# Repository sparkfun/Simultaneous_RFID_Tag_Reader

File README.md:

SparkFun Simultaneous RFID Tag Reader Breakout
=============================================

[* SparkFun Simultaneous RFID Tag Reader Breakout](https://www.sparkfun.com/products/14066)

A breakout board the for UHF RFID module (M6E-NANO) from ThingMagic. 
Capable of reading multiple 860-920MHz UHF RFID tags at the same time with increased read distance. 
You can also write to tags to boot. 

Board works either as shield or as stand alone device (using a USB to Serial converter).

Repository Contents
-------------------

* **/Documentation** - Data sheets, additional product information
* **/Hardware** - Eagle design files (.brd, .sch)
* **/Libraries** - Libraries for use with the Simultaneous RFID Tag Reader
* **/Production** - Production panel files (.brd)

Documentation
--------------
* **[Library](https://github.com/sparkfun/SparkFun_Simultaneous_RFID_Tag_Reader_Library)** - Arduino library for the Tag Reader.
* **[Hookup Guide](https://learn.sparkfun.com/tutorials/simultaneous-rfid-tag-reader-hookup-guide)** - Basic hookup guide for the Tag Reader.
* **[SparkFun Fritzing repo](https://github.com/sparkfun/Fritzing_Parts)** - Fritzing diagrams for SparkFun products.
* **[SparkFun 3D Model repo](https://github.com/sparkfun/3D_Models)** - 3D models of SparkFun products. 

License Information
-------------------

This product is _**open source**_! 

Please review the LICENSE.md file for license information. 

If you have any questions or concerns on licensing, please contact techsupport@sparkfun.com.

Distributed as-is; no warranty is given.

- Your friends at SparkFun.

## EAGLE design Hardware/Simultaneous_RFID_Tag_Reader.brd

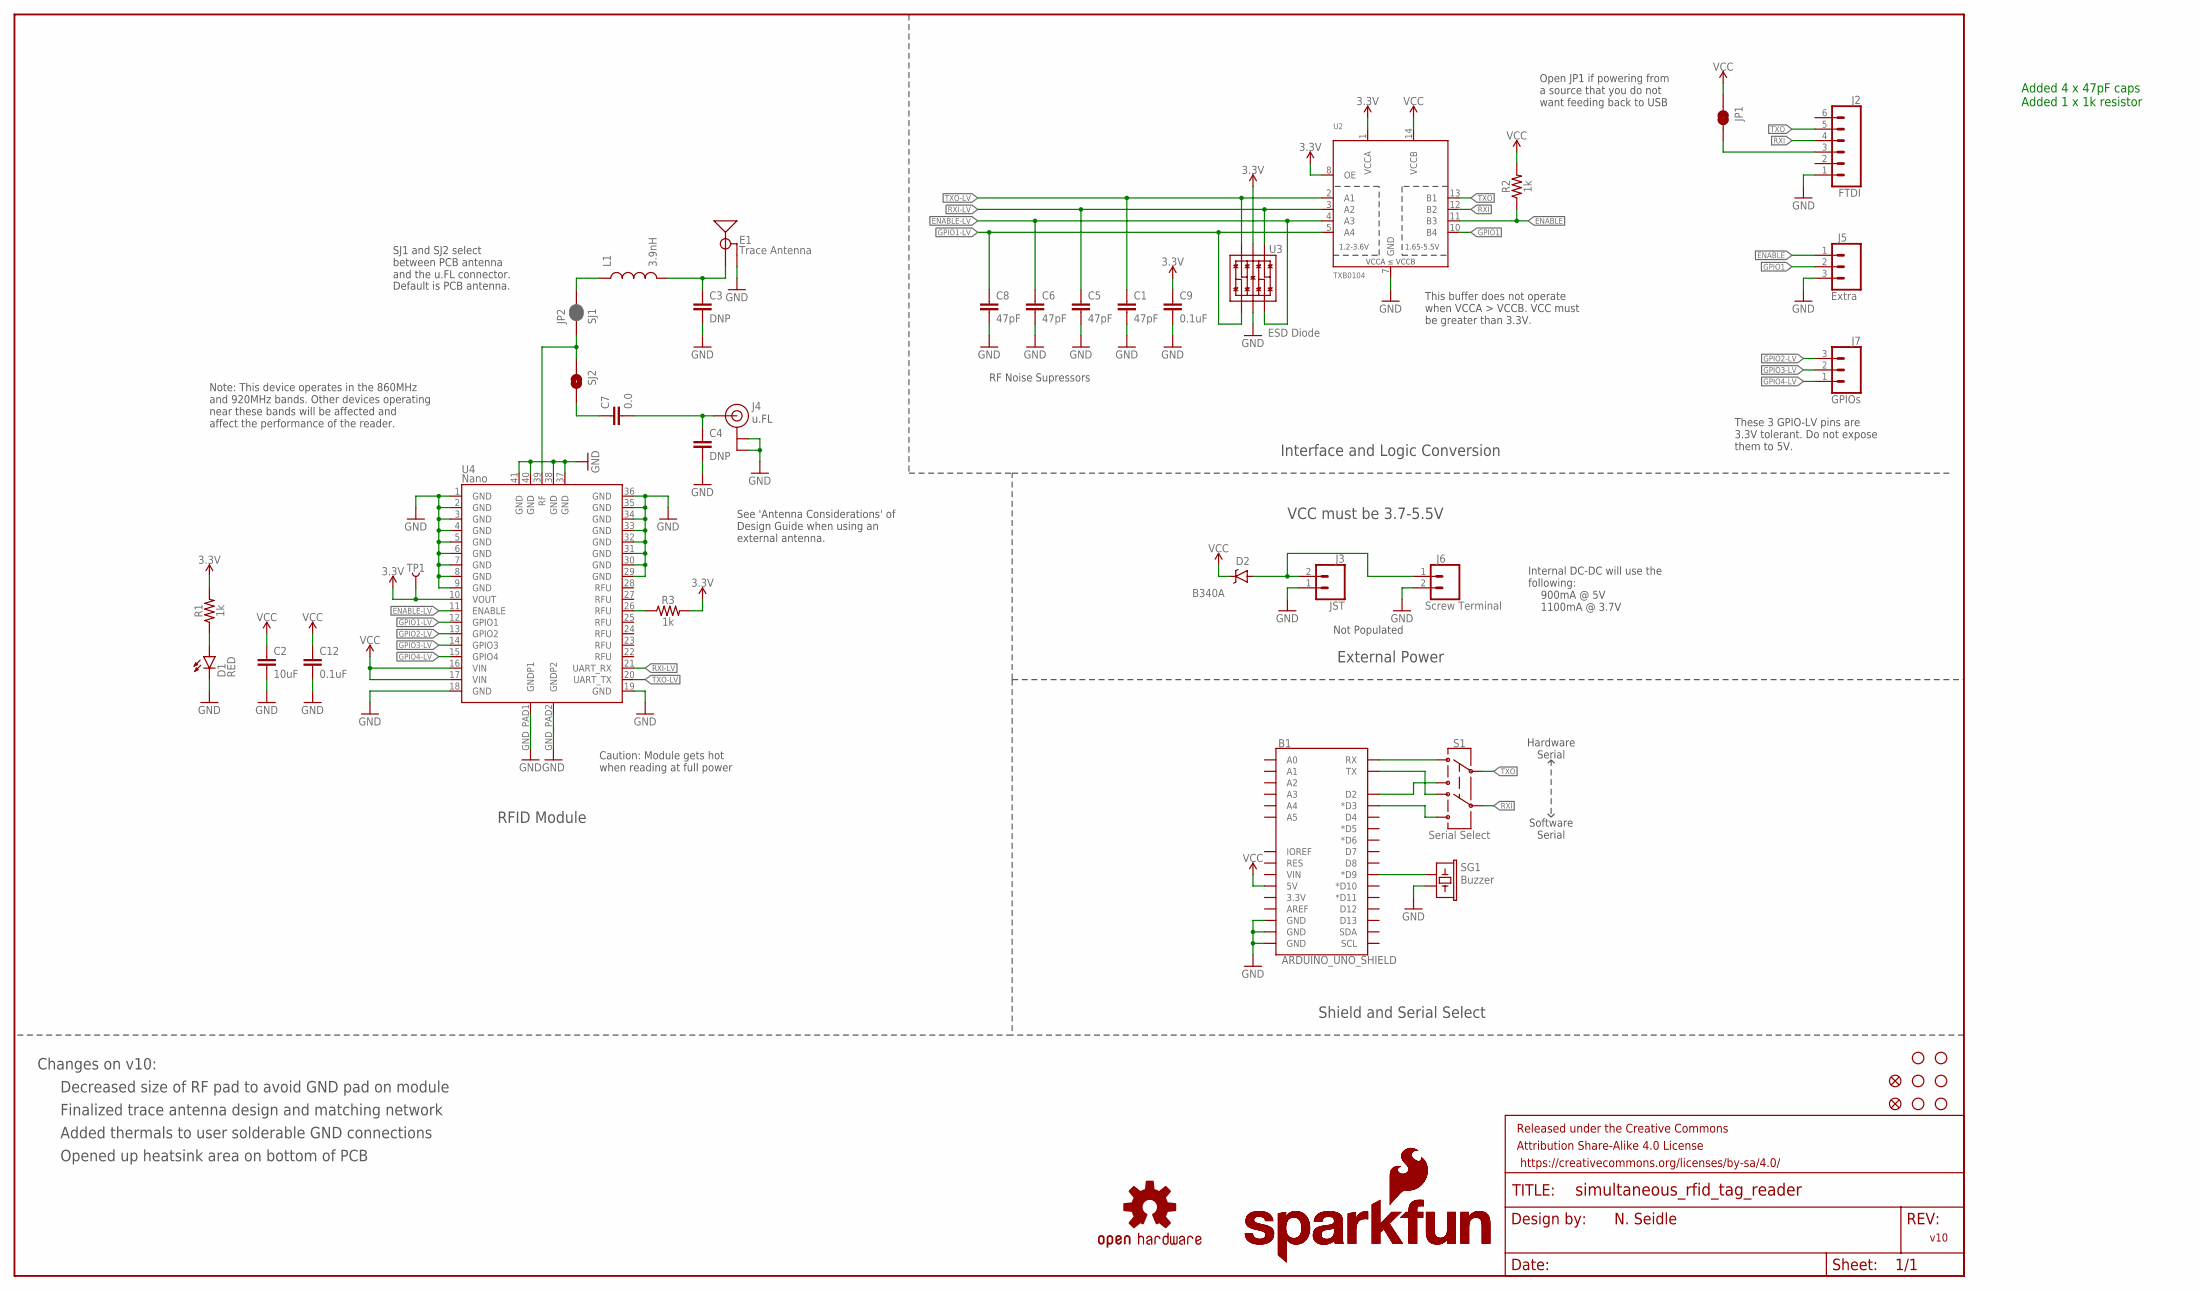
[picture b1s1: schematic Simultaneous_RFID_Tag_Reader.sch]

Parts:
B1: ARDUINO_UNO_SHIELD; UNO_R3_SHIELD
C1, C5, C6, C8: 47pF; 0603
C2: 10uF; 0805
C3, C4: DNP; 0603
C7: 0.0; 0603
C9, C12: 0.1uF; 0603
D1: RED; LED-0603
D2: B340A; SMA-DIODE
E1: Trace Antenna; 915MHZ_ANTENNA_TRIMBLE
FID1, FID2: FIDUCIAL1X2; FIDUCIAL-1X2
FRAME1: FRAME-LEDGER; CREATIVE_COMMONS
J2: FTDI; 1X06
J3: JST; JST-2-PTH
J4: U.FL
J5: Extra; 1X03
J6: Screw Terminal; SCREWTERMINAL-3.5MM-2
J7: GPIOs; 1X03
JP1: JUMPER-SMT_2_NC_TRACE_SILK; SMT-JUMPER_2_NC_TRACE_SILK
JP2: SJ1; SMT-JUMPER_2_NO_NO-SILK
L1: 3.9nH; 0603
LOGO1, LOGO3: SFE_LOGO_NAME_FLAME.1_INCH; SFE_LOGO_NAME_FLAME_.1
LOGO2: OSHW-LOGOS; OSHW-LOGO-S
R1, R2, R3: 1k; 0603
S1: Serial Select; SWITCH_DPDT_SMD_AYZ0202
SG1: Buzzer; BUZZER-CCV
SJ2: JUMPER-SMT_2_NO_NO-SILK; SMT-JUMPER_2_NO_NO-SILK
STANDOFF1, STANDOFF2, STANDOFF3, STANDOFF4, STANDOFF7, STANDOFF8: STAND-OFF
TP1: TEST-POINT3; PAD.03X.03
U2: TXB0104; SO14
U3: ESD Diode; SOT-23-6
U4: Nano; NANO_MODULE

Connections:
3.3V: C9.1, R1.2, R3.2, TP1.P$1, U2.1 (VCCA), U2.8 (OE), U3.5 (VCC), U4.10 (VOUT)
ANT3: JP2.1, SJ2.1, U4.39 (RF)
ENABLE: J5.1, R2.1, U2.11 (B3)
ENABLE-LV: C6.1, U2.4 (A3), U3.3 (IO2), U4.11 (ENABLE)
GND: B1.GND@0 (GND), B1.GND@1 (GND), B1.GND@2 (GND), C1.2, C2.2, C3.2, C4.2, C5.2, C6.2, C8.2, C9.2, C12.2, D1.C, E1.GND@1 (GND), E1.GND@2 (GND), E1.GND@3 (GND), J2.1, J3.1, J4.P$1 (GND), J4.P$2 (GND), J5.3, J6.2, SG1.- (2), U2.7 (GND), U3.2 (VSS), U4.1 (GND), U4.2 (GND), U4.3 (GND), U4.4 (GND), U4.5 (GND), U4.6 (GND), U4.7 (GND), U4.8 (GND), U4.9 (GND), U4.18 (GND), U4.19 (GND), U4.29 (GND), U4.30 (GND), U4.31 (GND), U4.32 (GND), U4.33 (GND), U4.34 (GND), U4.35 (GND), U4.36 (GND), U4.37 (GND), U4.38 (GND), U4.40 (GND), U4.41 (GND), U4.GND_PAD1 (GNDP1), U4.GND_PAD2 (GNDP2)
GPIO1: J5.2, U2.10 (B4)
GPIO1-LV: C8.1, U2.5 (A4), U3.1 (IO1), U4.12 (GPIO1)
GPIO2-LV: J7.3, U4.13 (GPIO2)
GPIO3-LV: J7.2, U4.14 (GPIO3)
GPIO4-LV: J7.1, U4.15 (GPIO4)
unnamed: C3.1, E1.ANT (SIGNAL), L1.2
unnamed: JP2.2, L1.1
unnamed: C7.1, SJ2.2
unnamed: R3.1, U4.26 (RFU)
unnamed: C4.1, C7.2, J4.P$3 (SIGNAL)
unnamed: D1.A, R1.1
unnamed: J2.3, JP1.2
unnamed: B1.RX, S1.1
unnamed: B1.TX, S1.4
unnamed: B1.D9 (*D9), SG1.+ (1)
unnamed: D2.A, J3.2, J6.1
RXI: J2.4, S1.5, U2.12 (B2)
RXI-LV: C5.1, U2.3 (A2), U3.4 (IO3), U4.21 (UART_RX)
SOFT-RX: B1.D2, S1.3
SOFT-TX: B1.D3 (*D3), S1.6
TXO: J2.5, S1.2, U2.13 (B1)
TXO-LV: C1.1, U2.2 (A1), U3.6 (IO4), U4.20 (UART_TX)
VCC: B1.5V, C2.1, C12.1, D2.C, JP1.1, R2.2, U2.14 (VCCB), U4.16 (VIN), U4.17 (VIN)

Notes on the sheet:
v10
N. Seidle
Interface and Logic Conversion
VCC must be 3.7-5.5V
Internal DC-DC will use the following: 900mA @ 5V 1100mA @ 3.7V
RFID Module
SJ1 and SJ2 select between PCB antenna and the u.FL connector.
Note: This device operates in the 860MHz and 920MHz bands. Other devices operating near these bands will be affected and affect the performance of the reader.
See 'Antenna Considerations' of Design Guide when using an external antenna.
u.FL
Hardware Serial
Software Serial
External Power
Shield and Serial Select
Default is PCB antenna.
Not Populated
Open JP1 if powering from a source that you do not want feeding back to USB
These 3 GPIO-LV pins are 3.3V tolerant. Do not expose them to 5V.
Decreased size of RF pad to avoid GND pad on module
Finalized trace antenna design and matching network
Changes on v10:
Added thermals to user solderable GND connections
Caution: Module gets hot when reading at full power
Opened up heatsink area on bottom of PCB
This buffer does not operate when VCCA > VCCB. VCC must be greater than 3.3V.
RF Noise Supressors
Added 4 x 47pF caps Added 1 x 1k resistor

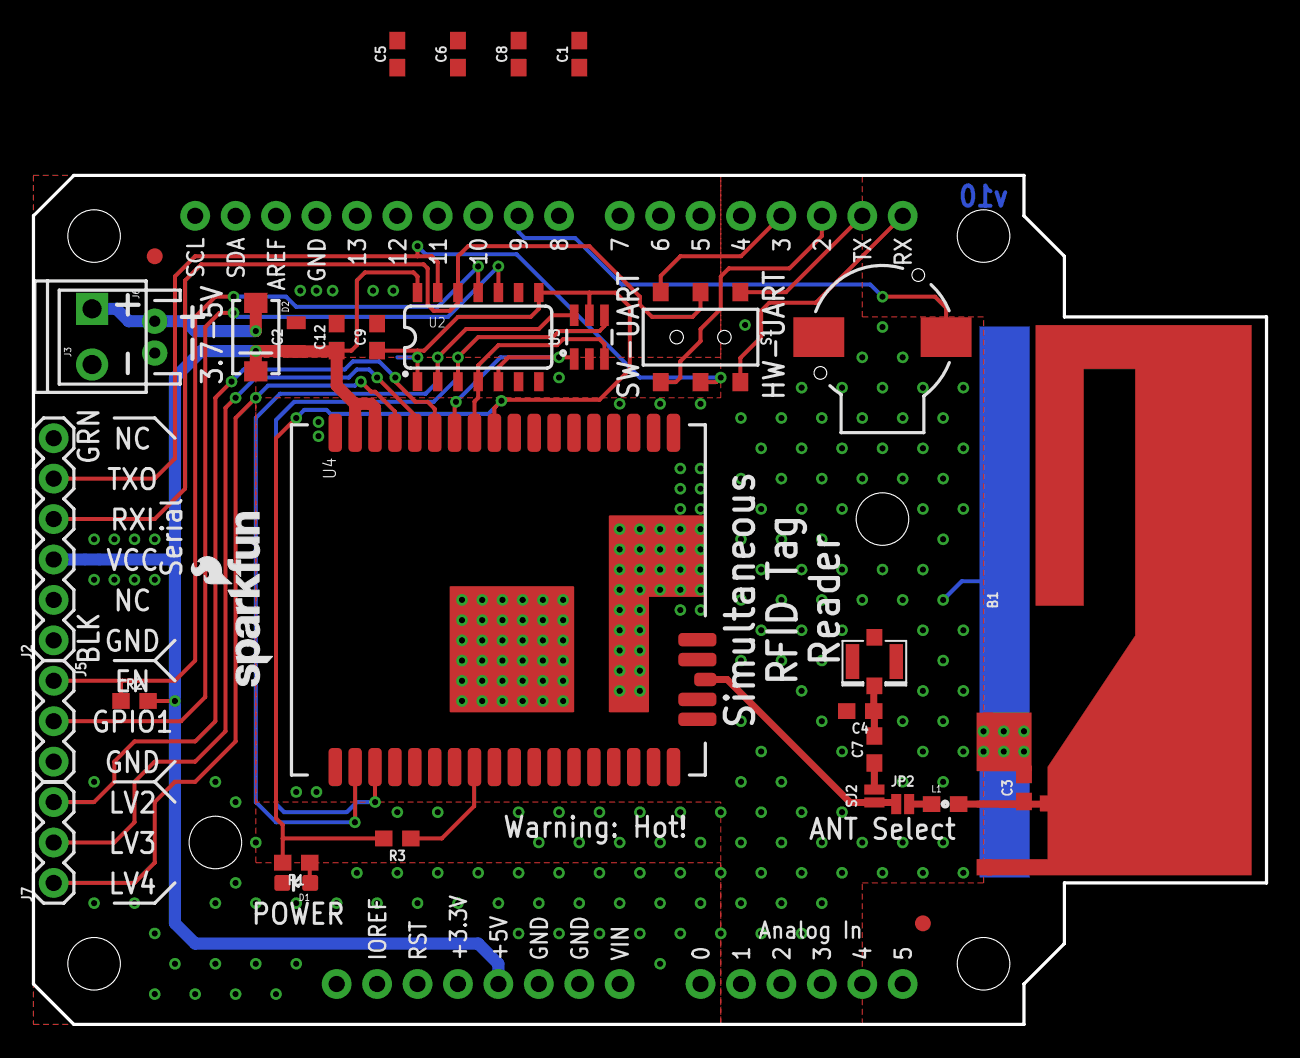
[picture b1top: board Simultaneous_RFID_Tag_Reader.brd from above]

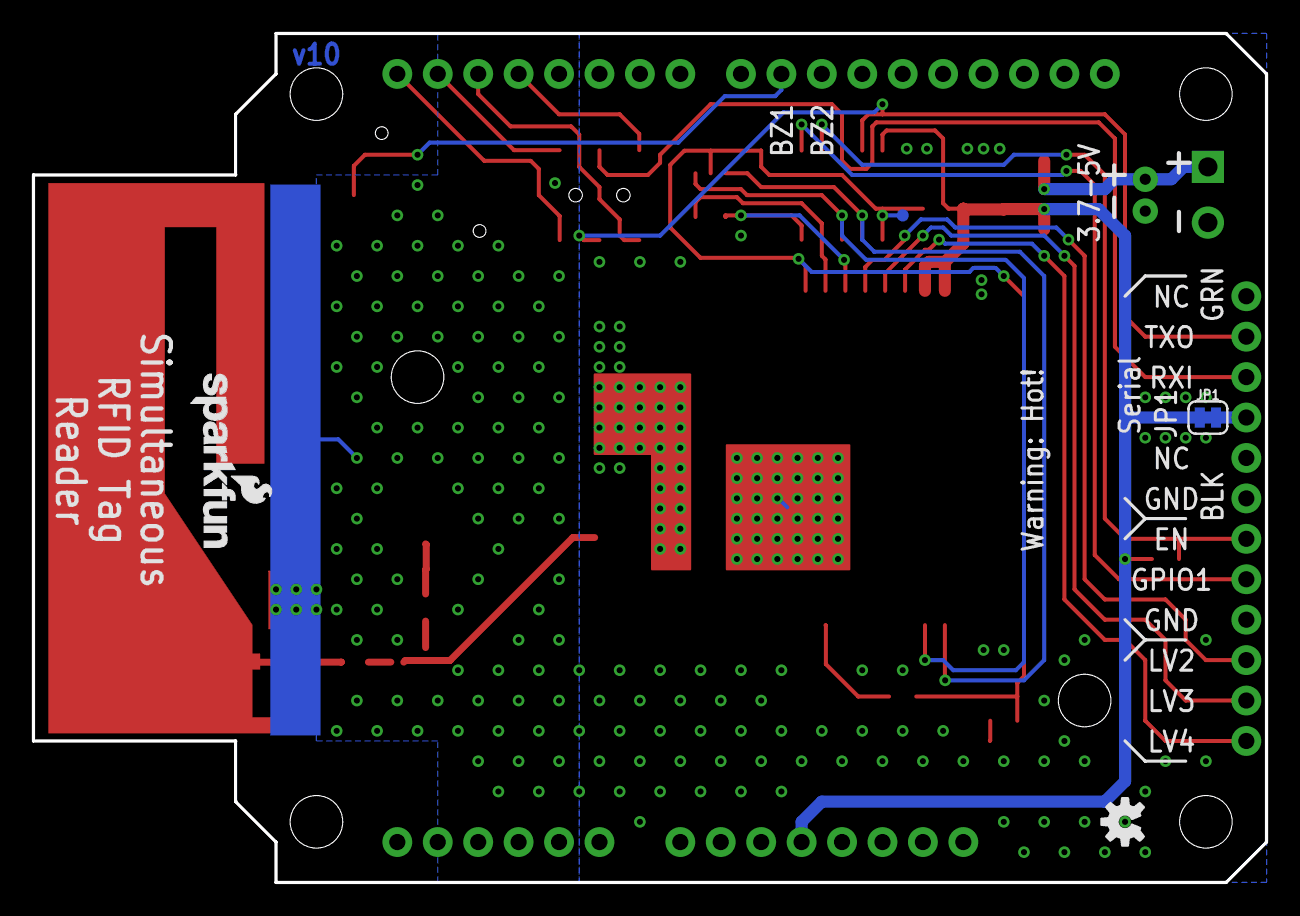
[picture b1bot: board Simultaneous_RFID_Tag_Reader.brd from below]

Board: 2 copper layers, 77.5 x 53.3 mm, 45 parts (4 on the bottom side), 28 nets.

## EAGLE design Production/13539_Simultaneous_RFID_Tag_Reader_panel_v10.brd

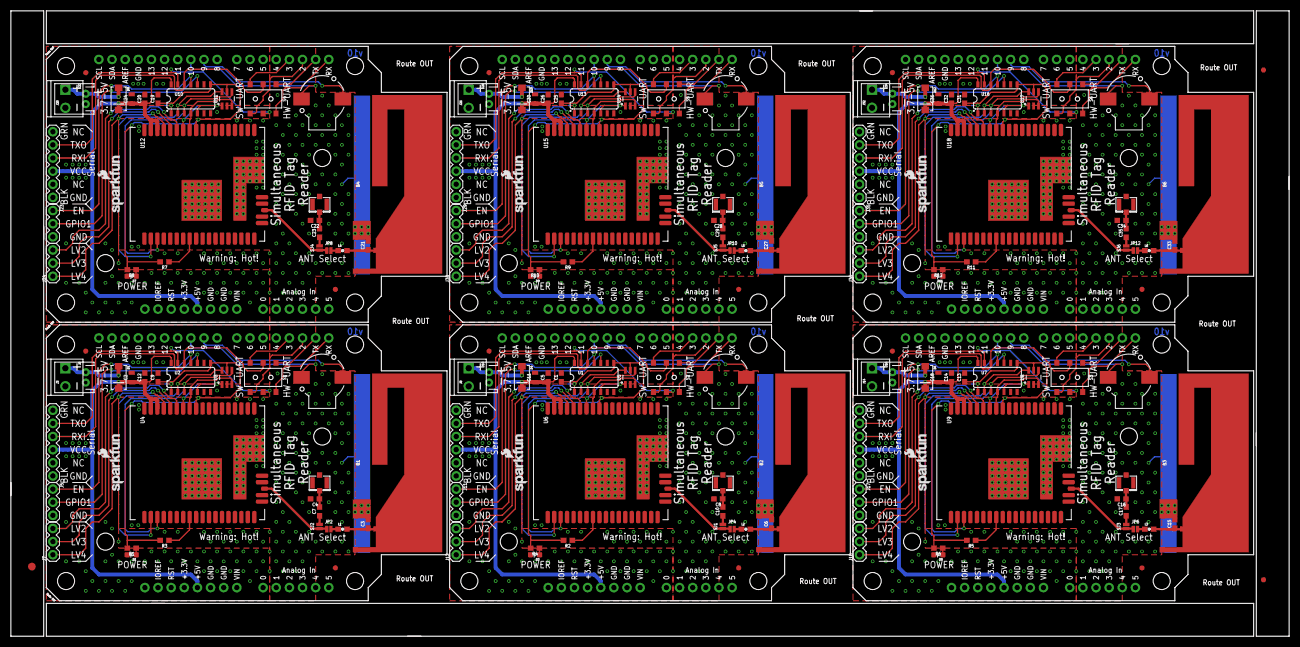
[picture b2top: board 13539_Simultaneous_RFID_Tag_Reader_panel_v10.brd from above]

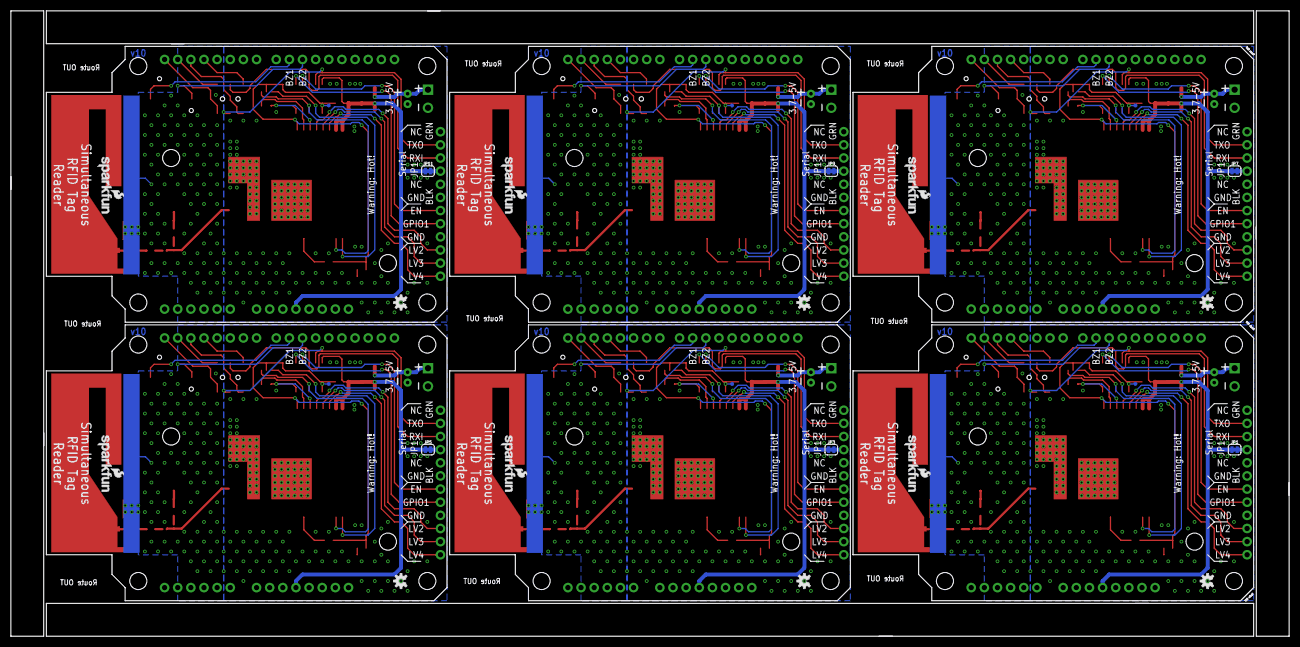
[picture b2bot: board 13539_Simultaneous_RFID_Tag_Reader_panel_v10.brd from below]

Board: 2 copper layers, 247.1 x 120.9 mm, 237 parts (24 on the bottom side), 174 nets.

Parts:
B1, B2, B3, B4, B5, B6: ARDUINO_UNO_SHIELD; UNO_R3_SHIELD
C1, C5, C9, C12, C13, C14, C19, C20, C25, C26, C31, C32: 0.1uF; 0603
C2, C11, C18, C24, C30, C36: 10uF; 0805
C3, C6, C15, C21, C27, C33: DNP; 0603
C4, C7, C8, C10, C16, C17, C22, C23, C28, C29, C34, C35: TBD; 0603
D1, D3, D5, D7, D9, D11: RED; LED-0603
D2, D4, D6, D8, D10, D12: B340A; SMA-DIODE
E1, E2, E3, E4, E5, E6: Trace Antenna; 915MHZ_ANTENNA_TRIMBLE
E$1: FIDUCIAL-1.5X3
E$7, E$8: FIDUCIAL-1X2
FID1, FID2, FID3, FID4, FID5, FID6, FID7, FID8, FID9, FID10, FID11, FID12: FIDUCIAL1X2; FIDUCIAL-1X2
J1, J2, J13, J19, J25, J31: FTDI; 1X06
J3, J8, J14, J20, J26, J32: JST; JST-2-PTH
J4, J9, J15, J21, J27, J33: U.FL
J5, J11, J17, J23, J29, J35: Extra; 1X03
J6, J10, J16, J22, J28, J34: Screw Terminal; SCREWTERMINAL-3.5MM-2
J7, J12, J18, J24, J30, J36: GPIOs; 1X03
JP1, JP3, JP5, JP7, JP9, JP11: SMT-JUMPER_2_NC_TRACE_SILK
JP2, JP4, JP6, JP8, JP10, JP12: SJ1; SMT-JUMPER_2_NO_NO-SILK
L1, L2, L3, L4, L5, L6: 3.9nH; 0603
LOGO1, LOGO3, LOGO4, LOGO6, LOGO7, LOGO9, LOGO10, LOGO12, LOGO13, LOGO15, LOGO16, LOGO18: SFE_LOGO_NAME_FLAME.1_INCH; SFE_LOGO_NAME_FLAME_.1
LOGO2, LOGO5, LOGO8, LOGO11, LOGO14, LOGO17: OSHW-LOGOS; OSHW-LOGO-S
R1, R2, R3, R4, R5, R6, R7, R8, R9, R10, R11, R12: 1k; 0603
S1, S2, S3, S4, S5, S6: Serial Select; SWITCH_DPDT_SMD_AYZ0202
SG1, SG2, SG3, SG4, SG5, SG6: Buzzer; BUZZER-CCV
SJ1, SJ2, SJ3, SJ4, SJ5, SJ6: SMT-JUMPER_2_NO_NO-SILK
STANDOFF1, STANDOFF2, STANDOFF3, STANDOFF4, STANDOFF5, STANDOFF6, STANDOFF7, STANDOFF8, STANDOFF9, STANDOFF10, STANDOFF11, STANDOFF12, STANDOFF13, STANDOFF14, STANDOFF15, STANDOFF16, STANDOFF17, STANDOFF18, STANDOFF19, STANDOFF20, STANDOFF21, STANDOFF22, STANDOFF23, STANDOFF24, STANDOFF25, STANDOFF26, STANDOFF27, STANDOFF28, STANDOFF29, STANDOFF30, STANDOFF31, STANDOFF32, STANDOFF33, STANDOFF34, STANDOFF35, STANDOFF36: STAND-OFF
TP1, TP2, TP3, TP4, TP5, TP6: PAD.03X.03
U1, U2, U7, U10, U13, U16: TXB0104; SO14
U3, U5, U8, U11, U14, U17: ESD Diode; SOT-23-6
U4, U6, U9, U12, U15, U18: Nano; NANO_MODULE

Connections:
3.3V: C9.1, R1.2, R3.2, TP1.P$1, U2.1, U2.8, U3.5, U4.10
3.3V1: C1.1, R2.2, R4.2, TP2.P$1, U1.1, U1.8, U5.5, U6.10
3.3V2: C13.1, R5.2, R6.2, TP3.P$1, U7.1, U7.8, U8.5, U9.10
3.3V3: C19.1, R7.2, R8.2, TP4.P$1, U10.1, U10.8, U11.5, U12.10
3.3V4: C25.1, R9.2, R10.2, TP5.P$1, U13.1, U13.8, U14.5, U15.10
3.3V5: C31.1, R11.2, R12.2, TP6.P$1, U16.1, U16.8, U17.5, U18.10
ANT1: JP4.1, SJ1.1, U6.39
ANT2: JP6.1, SJ3.1, U9.39
ANT3: JP2.1, SJ2.1, U4.39
ANT4: JP8.1, SJ4.1, U12.39
ANT5: JP10.1, SJ5.1, U15.39
ANT6: JP12.1, SJ6.1, U18.39
ENABLE: J5.1, U2.11
ENABLE1: J11.1, U1.11
ENABLE2: J17.1, U7.11
ENABLE3: J23.1, U10.11
ENABLE4: J29.1, U13.11
ENABLE5: J35.1, U16.11
ENABLE-LV: U2.4, U3.3, U4.11
ENABLE-LV1: U1.4, U5.3, U6.11
ENABLE-LV2: U7.4, U8.3, U9.11
ENABLE-LV3: U10.4, U11.3, U12.11
ENABLE-LV4: U13.4, U14.3, U15.11
ENABLE-LV5: U16.4, U17.3, U18.11
GND: B1.GND@0, B1.GND@1, B1.GND@2, C2.2, C3.2, C4.2, C9.2, C12.2, D1.C, E1.GND@1, E1.GND@2, E1.GND@3, J2.1, J3.1, J4.P$1, J4.P$2, J5.3, J6.2, U2.7, U3.2, U4.1, U4.2, U4.3, U4.4, U4.5, U4.6, U4.7, U4.8, U4.9, U4.18, U4.19, U4.29, U4.30, U4.31, U4.32, U4.33, U4.34, U4.35, U4.36, U4.37, U4.38, U4.40, U4.41, U4.GND_PAD2
GND1: B2.GND@0, B2.GND@1, B2.GND@2, C1.2, C5.2, C6.2, C8.2, C11.2, D3.C, E2.GND@1, E2.GND@2, E2.GND@3, J1.1, J8.1, J9.P$1, J9.P$2, J10.2, J11.3, U1.7, U5.2, U6.1, U6.2, U6.3, U6.4, U6.5, U6.6, U6.7, U6.8, U6.9, U6.18, U6.19, U6.29, U6.30, U6.31, U6.32, U6.33, U6.34, U6.35, U6.36, U6.37, U6.38, U6.40, U6.41, U6.GND_PAD2
GND2: B3.GND@0, B3.GND@1, B3.GND@2, C13.2, C14.2, C15.2, C16.2, C18.2, D5.C, E3.GND@1, E3.GND@2, E3.GND@3, J13.1, J14.1, J15.P$1, J15.P$2, J16.2, J17.3, U7.7, U8.2, U9.1, U9.2, U9.3, U9.4, U9.5, U9.6, U9.7, U9.8, U9.9, U9.18, U9.19, U9.29, U9.30, U9.31, U9.32, U9.33, U9.34, U9.35, U9.36, U9.37, U9.38, U9.40, U9.41, U9.GND_PAD2
GND3: B4.GND@0, B4.GND@1, B4.GND@2, C19.2, C20.2, C21.2, C22.2, C24.2, D7.C, E4.GND@1, E4.GND@2, E4.GND@3, J19.1, J20.1, J21.P$1, J21.P$2, J22.2, J23.3, U10.7, U11.2, U12.1, U12.2, U12.3, U12.4, U12.5, U12.6, U12.7, U12.8, U12.9, U12.18, U12.19, U12.29, U12.30, U12.31, U12.32, U12.33, U12.34, U12.35, U12.36, U12.37, U12.38, U12.40, U12.41, U12.GND_PAD2
GND4: B5.GND@0, B5.GND@1, B5.GND@2, C25.2, C26.2, C27.2, C28.2, C30.2, D9.C, E5.GND@1, E5.GND@2, E5.GND@3, J25.1, J26.1, J27.P$1, J27.P$2, J28.2, J29.3, U13.7, U14.2, U15.1, U15.2, U15.3, U15.4, U15.5, U15.6, U15.7, U15.8, U15.9, U15.18, U15.19, U15.29, U15.30, U15.31, U15.32, U15.33, U15.34, U15.35, U15.36, U15.37, U15.38, U15.40, U15.41, U15.GND_PAD2
GND5: B6.GND@0, B6.GND@1, B6.GND@2, C31.2, C32.2, C33.2, C34.2, C36.2, D11.C, E6.GND@1, E6.GND@2, E6.GND@3, J31.1, J32.1, J33.P$1, J33.P$2, J34.2, J35.3, U16.7, U17.2, U18.1, U18.2, U18.3, U18.4, U18.5, U18.6, U18.7, U18.8, U18.9, U18.18, U18.19, U18.29, U18.30, U18.31, U18.32, U18.33, U18.34, U18.35, U18.36, U18.37, U18.38, U18.40, U18.41, U18.GND_PAD2
GPIO1: J5.2, U2.10
GPIO1-LV: U2.5, U3.1, U4.12
GPIO1-LV1: U1.5, U5.1, U6.12
GPIO1-LV2: U7.5, U8.1, U9.12
GPIO1-LV3: U10.5, U11.1, U12.12
GPIO1-LV4: U13.5, U14.1, U15.12
GPIO1-LV5: U16.5, U17.1, U18.12
GPIO2: J11.2, U1.10
GPIO2-LV: J7.3, U4.13
GPIO2-LV1: J12.3, U6.13
GPIO2-LV2: J18.3, U9.13
GPIO2-LV3: J24.3, U12.13
GPIO2-LV4: J30.3, U15.13
GPIO2-LV5: J36.3, U18.13
GPIO3: J17.2, U7.10
GPIO3-LV: J7.2, U4.14
GPIO3-LV1: J12.2, U6.14
GPIO3-LV2: J18.2, U9.14
GPIO3-LV3: J24.2, U12.14
GPIO3-LV4: J30.2, U15.14
GPIO3-LV5: J36.2, U18.14
GPIO4: J23.2, U10.10
GPIO4-LV: J7.1, U4.15
GPIO4-LV1: J12.1, U6.15
GPIO4-LV2: J18.1, U9.15
GPIO4-LV3: J24.1, U12.15
GPIO4-LV4: J30.1, U15.15
GPIO4-LV5: J36.1, U18.15
GPIO5: J29.2, U13.10
GPIO6: J35.2, U16.10
unnamed: C3.1, E1.ANT, L1.2
unnamed: JP2.2, L1.1
unnamed: C7.1, SJ2.2
unnamed: R3.1, U4.26
unnamed: C4.1, C7.2, J4.P$3
unnamed: D1.A, R1.1
unnamed: J2.3, JP1.2
unnamed: B1.RX, S1.1
unnamed: B1.TX, S1.4
unnamed: B1.D9, SG1.+
unnamed: D2.A, J3.2, J6.1
unnamed: B1.D10, SG1.-
unnamed: R2.1, U6.26
unnamed: B2.RX, S2.1
unnamed: B2.TX, S2.4
unnamed: C6.1, E2.ANT, L2.2
unnamed: JP4.2, L2.1
unnamed: C10.1, SJ1.2
unnamed: C8.1, C10.2, J9.P$3
unnamed: D3.A, R4.1
unnamed: J1.3, JP3.2
unnamed: D4.A, J8.2, J10.1
unnamed: B2.D9, SG2.+
unnamed: B2.D10, SG2.-
unnamed: R5.1, U9.26
unnamed: B3.RX, S3.1
unnamed: B3.TX, S3.4
unnamed: C15.1, E3.ANT, L3.2
unnamed: JP6.2, L3.1
unnamed: C17.1, SJ3.2
unnamed: C16.1, C17.2, J15.P$3
unnamed: D5.A, R6.1
unnamed: J13.3, JP5.2
unnamed: D6.A, J14.2, J16.1
unnamed: B3.D9, SG3.+
unnamed: B3.D10, SG3.-
unnamed: R7.1, U12.26
unnamed: B4.RX, S4.1
unnamed: B4.TX, S4.4
unnamed: C21.1, E4.ANT, L4.2
unnamed: JP8.2, L4.1
unnamed: C23.1, SJ4.2
unnamed: C22.1, C23.2, J21.P$3
unnamed: D7.A, R8.1
unnamed: J19.3, JP7.2
unnamed: D8.A, J20.2, J22.1
unnamed: B4.D9, SG4.+
unnamed: B4.D10, SG4.-
unnamed: R9.1, U15.26
unnamed: B5.RX, S5.1
unnamed: B5.TX, S5.4
unnamed: C27.1, E5.ANT, L5.2
unnamed: JP10.2, L5.1
unnamed: C29.1, SJ5.2
unnamed: C28.1, C29.2, J27.P$3
unnamed: D9.A, R10.1
unnamed: J25.3, JP9.2
unnamed: D10.A, J26.2, J28.1
unnamed: B5.D9, SG5.+
unnamed: B5.D10, SG5.-
unnamed: R11.1, U18.26
unnamed: B6.RX, S6.1
unnamed: B6.TX, S6.4
unnamed: C33.1, E6.ANT, L6.2
unnamed: JP12.2, L6.1
unnamed: C35.1, SJ6.2
unnamed: C34.1, C35.2, J33.P$3
unnamed: D11.A, R12.1
unnamed: J31.3, JP11.2
unnamed: D12.A, J32.2, J34.1
unnamed: B6.D9, SG6.+
unnamed: B6.D10, SG6.-
RXI: J2.4, S1.5, U2.12
RXI1: J1.4, S2.5, U1.12
RXI2: J13.4, S3.5, U7.12
RXI3: J19.4, S4.5, U10.12
RXI4: J25.4, S5.5, U13.12
RXI5: J31.4, S6.5, U16.12
RXI-LV: U2.3, U3.4, U4.21
RXI-LV1: U1.3, U5.4, U6.21
RXI-LV2: U7.3, U8.4, U9.21
RXI-LV3: U10.3, U11.4, U12.21
RXI-LV4: U13.3, U14.4, U15.21
RXI-LV5: U16.3, U17.4, U18.21
SOFT-RX: B1.D2, S1.3
SOFT-RX1: B2.D2, S2.3
SOFT-RX2: B3.D2, S3.3
SOFT-RX3: B4.D2, S4.3
SOFT-RX4: B5.D2, S5.3
SOFT-RX5: B6.D2, S6.3
SOFT-TX: B1.D3, S1.6
SOFT-TX1: B2.D3, S2.6
SOFT-TX2: B3.D3, S3.6
SOFT-TX3: B4.D3, S4.6
SOFT-TX4: B5.D3, S5.6
SOFT-TX5: B6.D3, S6.6
TXO: J2.5, S1.2, U2.13
TXO1: J1.5, S2.2, U1.13
TXO2: J13.5, S3.2, U7.13
TXO3: J19.5, S4.2, U10.13
TXO4: J25.5, S5.2, U13.13
TXO5: J31.5, S6.2, U16.13
TXO-LV: U2.2, U3.6, U4.20
TXO-LV1: U1.2, U5.6, U6.20
TXO-LV2: U7.2, U8.6, U9.20
TXO-LV3: U10.2, U11.6, U12.20
TXO-LV4: U13.2, U14.6, U15.20
TXO-LV5: U16.2, U17.6, U18.20
VCC: B1.5V, C2.1, C12.1, D2.C, JP1.1, U2.14, U4.16, U4.17
VCC1: B2.5V, C5.1, C11.1, D4.C, JP3.1, U1.14, U6.16, U6.17
VCC2: B3.5V, C14.1, C18.1, D6.C, JP5.1, U7.14, U9.16, U9.17
VCC3: B4.5V, C20.1, C24.1, D8.C, JP7.1, U10.14, U12.16, U12.17
VCC4: B5.5V, C26.1, C30.1, D10.C, JP9.1, U13.14, U15.16, U15.17
VCC5: B6.5V, C32.1, C36.1, D12.C, JP11.1, U16.14, U18.16, U18.17

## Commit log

2016-10-05 :circus_tent: Added .gitattributes & .gitignore files
2016-10-05 Many changes from design review
2016-10-06 Fixed problems found during review
2016-10-10 Fixed airwire
2016-10-13 Library additions. Writing not yet working.
2016-10-20 Update to examples - work in progress.
2016-10-25 Finalizing antenna. Adding buzzer.
2016-11-01 Added heat sink area and mounting holes.
2016-11-01 Adding buzzer labels
2016-11-07 Changing input silk to 3.7-5V.
2016-11-15 panel
2016-11-22 Finishing matching network to u.FL
2016-12-15 Adding cosmetic GND connection to schematic.
2017-01-18 Added insulation to ISP and ground thermal. Added RF supressors to enable. Grounded half of buzzer.
2017-01-18 Adding dims to board. Updating readme.
2017-01-18 Squashed 'Libraries/Arduino/' content from commit 09f6561
    git-subtree-dir: Libraries/Arduino
    git-subtree-split: 09f65617289656be7bcbb42c2a57301124a67a72
2017-01-25 Adding pull up to enable pin
    TXB0104 wants unused inputs to be in same state. This pull up does that
    for the HV side.
2017-02-22 Update README.md
    Adding product/documentation links
2017-02-24 Squashed 'Libraries/Arduino/' changes from 09f6561..d445e0f
    d445e0f Incrementing library version
    3fe6b17 Fixed bug: don't call printArray unless debug port has been defined.
    ef7f551 Renaming of example fines
    d9fd735 Renaming of example files
    git-subtree-dir: Libraries/Arduino
    git-subtree-split: d445e0fc11d1f5940b91b91c6c6669cd72d339cb
2019-04-27 Removing library from hardware repo

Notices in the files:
parts and their libraries:
SparkFun-Aesthetics: Licensing: CC v3.0 Share-Alike You are welcome to use this library for commercial purposes.
SparkFun-Aesthetics: Released under the Creative Commons Attribution Share-Alike 4.0 License
SparkFun-Aesthetics: https://creativecommons.org/licenses/by-sa/4.0
